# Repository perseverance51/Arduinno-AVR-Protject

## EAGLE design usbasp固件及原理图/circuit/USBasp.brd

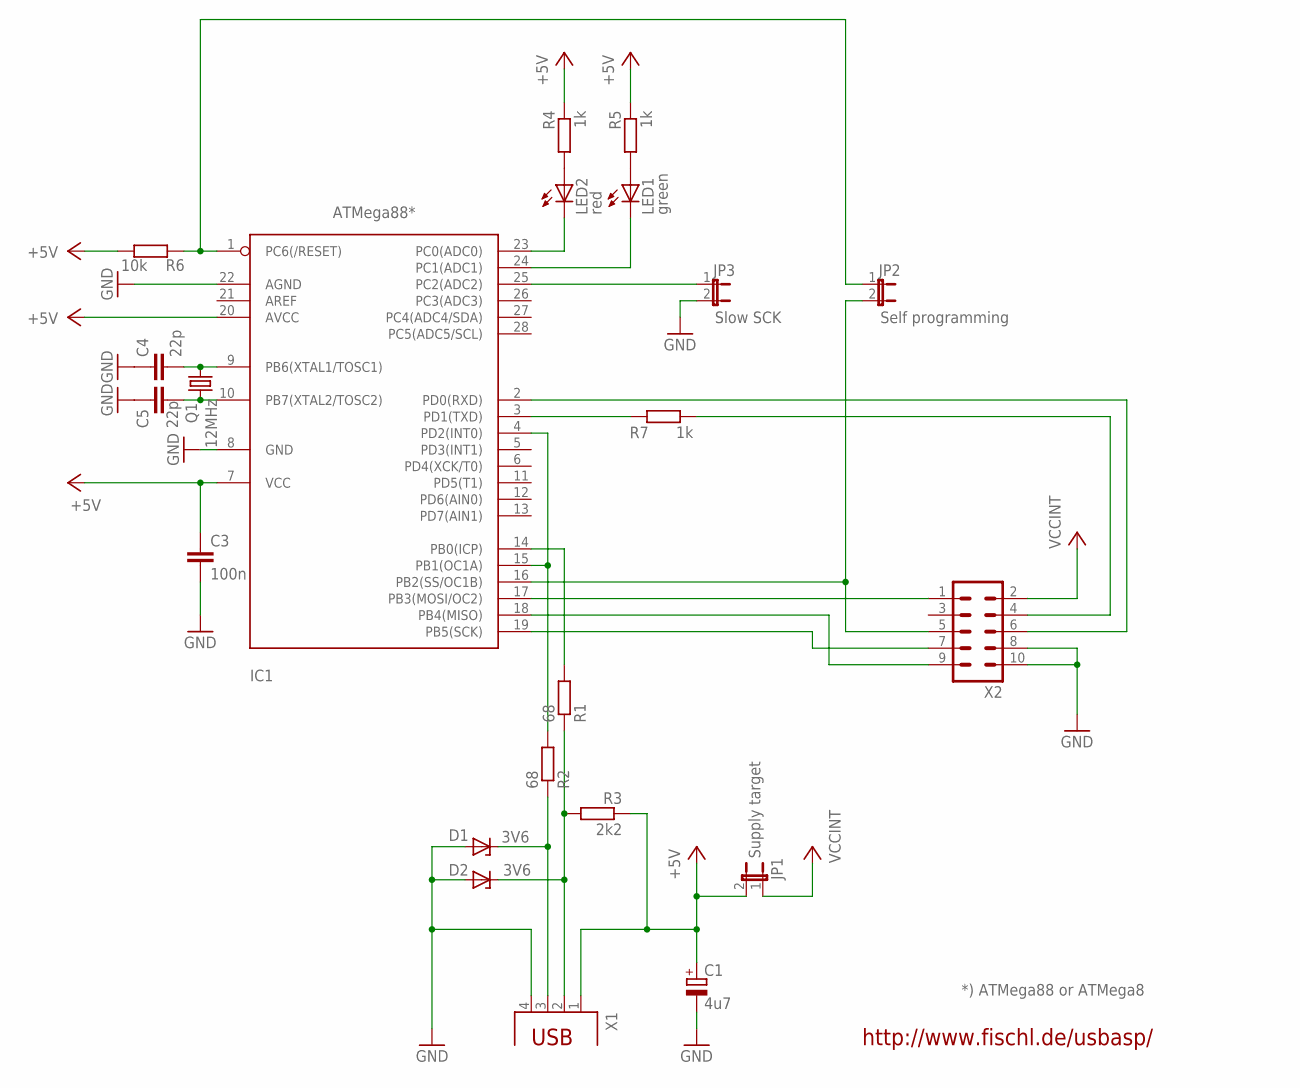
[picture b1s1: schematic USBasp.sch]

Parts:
C1: 4u7; E2,5-5
C3: 100n; C025-024X044
C4, C5: 22p; C025-024X044
D1, D2: 3V6; DO34Z7
IC1: ATMega88*; DIL28-3
JP1: Supply target; JP1
JP2: Self programming; JP1
JP3: Slow SCK; JP1
LED1: green; LED3MM
LED2: red; LED3MM
Q1: 12MHz; HC49/S
R1, R2: 68; 0207/10
R3: 2k2; 0207/10
R4, R5, R7: 1k; 0207/10
R6: 10k; 0207/10
X1: PN61729
X2: ML10L

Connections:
+5V: C1.+, C3.1, IC1.7 (VCC), IC1.20 (AVCC), JP1.2, R3.1, R4.1, R5.1, R6.1, X1.1
GND: C1.-, C3.2, C4.1, C5.1, D1.A, D2.A, IC1.8 (GND), IC1.22 (AGND), JP3.2, X1.4, X2.8, X2.10
unnamed: IC1.1 (PC6(/RESET)), JP2.1, R6.2
unnamed: IC1.16 (PB2(SS/OC1B)), JP2.2, X2.5
unnamed: IC1.17 (PB3(MOSI/OC2)), X2.1
unnamed: IC1.19 (PB5(SCK)), X2.7
unnamed: D2.C, R1.1, R3.2, X1.2
unnamed: IC1.18 (PB4(MISO)), X2.9
unnamed: IC1.4 (PD2(INT0)), IC1.15 (PB1(OC1A)), R2.2
unnamed: D1.C, R2.1, X1.3
unnamed: IC1.3 (PD1(TXD)), R7.2
unnamed: R7.1, X2.4
unnamed: IC1.2 (PD0(RXD)), X2.6
unnamed: IC1.25 (PC2(ADC2)), JP3.1
unnamed: LED2.A, R4.2
unnamed: IC1.23 (PC0(ADC0)), LED2.K (C)
unnamed: IC1.24 (PC1(ADC1)), LED1.K (C)
unnamed: IC1.14 (PB0(ICP)), R1.2
unnamed: C4.2, IC1.9 (PB6(XTAL1/TOSC1)), Q1.2
unnamed: C5.2, IC1.10 (PB7(XTAL2/TOSC2)), Q1.1
unnamed: LED1.A, R5.2
VCCINT: JP1.1, X2.2

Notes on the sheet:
http://www.fischl.de/usbasp/
*) ATMega88 or ATMega8

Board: 2 copper layers, 22 parts (0 on the bottom side), 22 nets, no tracks yet.

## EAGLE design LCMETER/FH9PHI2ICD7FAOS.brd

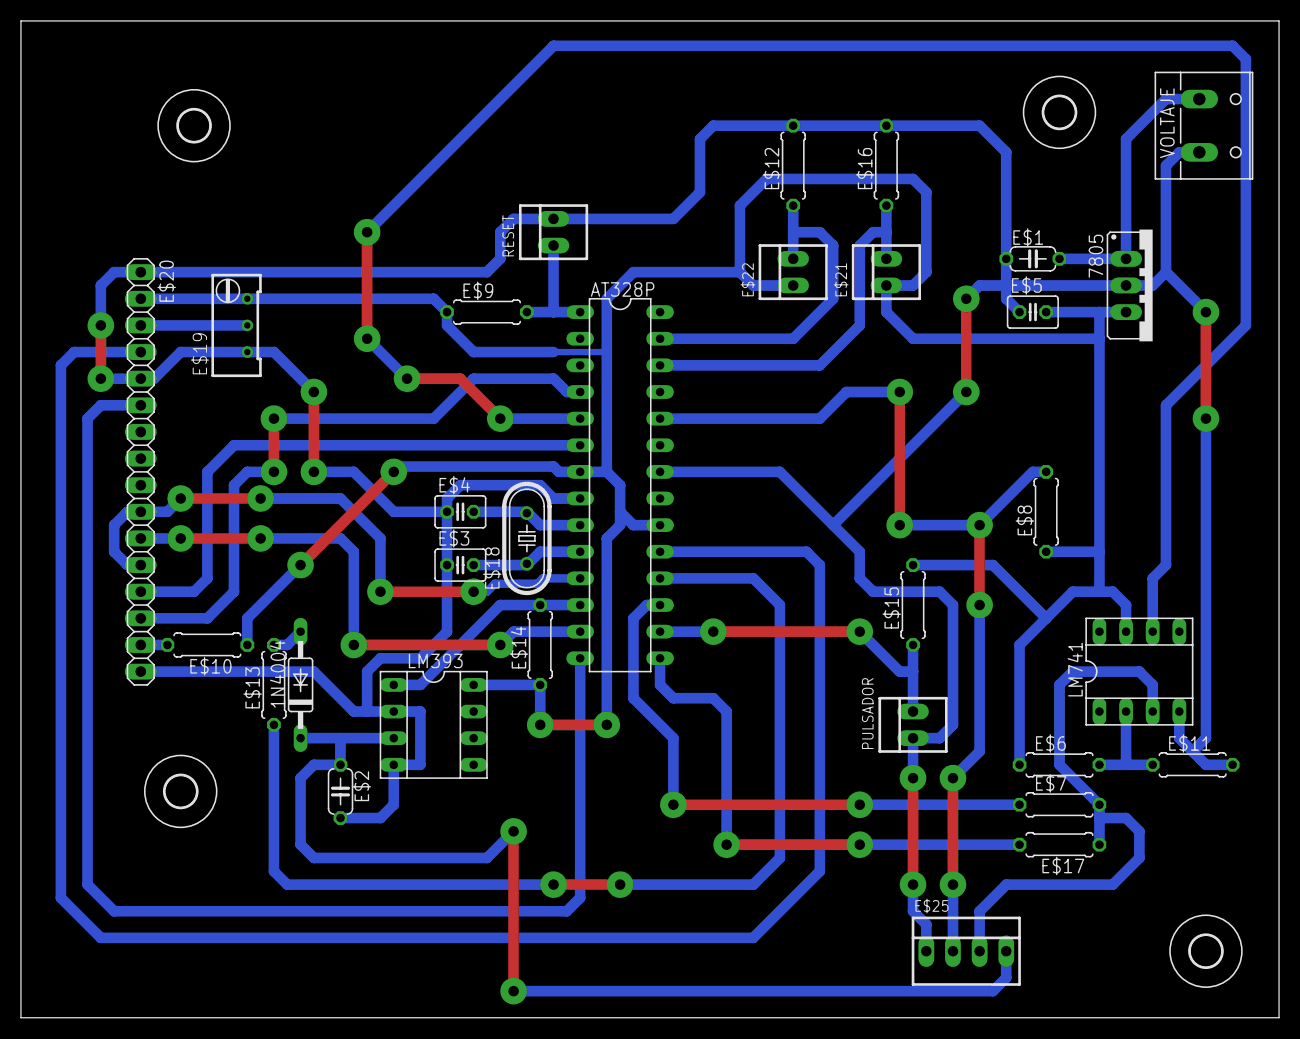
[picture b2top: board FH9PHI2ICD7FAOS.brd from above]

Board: 2 copper layers, 120.0 x 95.1 mm, 35 parts (0 on the bottom side), 28 nets.

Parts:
1N4004: C2992
7805: 78XXS
AT328P: DIL28-3
E$1: 0.33uF; C050-024X044
E$2: 1uF; C050-024X044
E$3, E$4: 22pF; C025-030X050
E$5: 100nF; C025-030X050
E$6, E$8, E$9, E$11, E$12, E$15, E$16: 10k; 0207/7
E$7: 1M; 0207/7
E$10, E$17: 220; 0207/7
E$13: 150; 0207/7
E$14: 330; 0207/7
E$18: 16Mhz; HC49/S
E$19: 10k; RTRIM64W
E$20: 1X16
E$21, E$22: 22-23-2021
E$23, E$24, E$26, E$27: 3,0
E$25: 22-23-2041
LM393, LM741: SOCKET-08
PULSADOR: 22-23-2021
RESET: 22-23-2021
VOLTAJE: W237-132

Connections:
S$1: AT328P.10, E$3.2
S$2: AT328P.9, E$4.2
S$4: AT328P.1, E$9.2, RESET.1
S$5: AT328P.11, E$20.12
S$6: 1N4004.C, E$2.1, E$25.4, LM393.3
S$7: AT328P.18, E$13.1
S$8: AT328P.12, LM393.1
S$9: 1N4004.A, E$13.2
S$10: AT328P.16, E$15.1, PULSADOR.2
S$11: E$19.2, E$20.3
S$12: AT328P.19, E$20.4
S$13: E$10.2, E$20.15
S$14: AT328P.14, E$20.6
S$15: AT328P.6, E$20.13
S$16: AT328P.4, E$20.14
S$17: E$6.2, E$11.1, LM741.2
S$18: AT328P.24, E$8.2, E$25.2
S$19: AT328P.13, E$20.11
S$20: E$17.1, E$25.3, LM741.3
S$21: AT328P.27, E$12.1, E$22.2
S$22: AT328P.8, E$2.2, E$3.1, E$4.1, E$20.16, LM393.2, LM393.4
S$23: AT328P.26, E$16.1, E$21.2
S$24: 7805.OUT, AT328P.7, AT328P.20, E$5.2, E$6.1, E$8.1, E$9.1, E$14.1, E$15.2, E$19.3, E$20.2, E$21.1, E$22.1, LM393.8, LM741.7
S$26: 7805.GND, AT328P.22, E$1.1, E$5.1, E$11.2, E$12.2, E$16.2, E$19.1, E$20.1, E$20.5, E$25.1, LM741.4, PULSADOR.1, RESET.2
S$28: AT328P.15, E$17.2
S$29: AT328P.5, LM741.6
S$31: AT328P.17, E$7.1
S$34: 7805.IN, E$1.2

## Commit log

2022-06-30 updown
